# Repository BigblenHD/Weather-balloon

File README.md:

# Atmospheric Data Acquisition — Weather Balloon

Embedded firmware and custom PCB design for an atmospheric measurement payload, developed as a school project in Luxembourg.

**My contribution:** firmware development, PCB design and technical project delivery. The project brought together sensor integration, data logging, electronics assembly and launch preparation.

## Flight outcome

The original team log records a launch from Redange on **14 September 2024**, followed by recovery near Verdun, France, roughly two hours later. The payload, camera and SD card were recovered intact. The flight dataset is not included in this repository.

## Engineering work

- Integrated environmental and motion sensors using I²C and SPI.
- Developed Arduino sketches for individual sensor checks and combined acquisition.
- Implemented timestamped SD-card logging and LED status indications.
- Designed the data-logger schematic and board layout in EAGLE.

## Start here

| Area | Files | What to review |
| --- | --- | --- |
| Combined acquisition | [`all_in_one.ino`](Prep_launch/Module_software_tests/all_in_one/all_in_one.ino) | Environmental sensors, IMU, ozone, gamma sensor, PT100, RTC and SD integration |
| Smaller logger variant | [`Final_Code.ino`](Prep_launch/Final%20Code/Final_Code.ino) | BMP280 + MPU6050 acquisition and CSV-style logging |
| Hardware | [PCB files](Prep_launch/PCB) | EAGLE `.sch` schematic and `.brd` layout |
| Component experiments | [Module tests](Prep_launch/Module_software_tests) | Isolated checks and calibration sketches |

## Hardware and dependencies

The repository contains several hardware revisions. Select dependencies for the sketch you are examining; the sketches are not interchangeable.

| Sketch | Components / libraries |
| --- | --- |
| `all_in_one.ino` | Adafruit MS8607, Adafruit Unified Sensor, DFRobot OzoneSensor, Arduino LSM9DS1, Adafruit MAX31865, RTClib, SD, Wire and SPI; GDK101 access is implemented in the sketch |
| `Final_Code.ino` | MPU6050_light, Adafruit BMP280 and its dependencies, SD, Wire and SPI |

Use the Arduino IDE and a board core compatible with the selected hardware. Board selection, library versions, wiring and calibration must be matched to the original build; a reproducible build configuration is not yet recorded.

## Working with the code

1. Start with the individual [module tests](Prep_launch/Module_software_tests) to understand each peripheral.
2. Install the libraries used by your chosen sketch.
3. Match sensor addresses, chip-select pins and LED pins to the board schematic.
4. Open the sketch in the Arduino IDE, keeping any companion `.h` and `.cpp` files together.
5. Check serial output and SD logging on the bench before combining peripherals.

The folder name `Final Code` describes a historical revision. Its sketch uses BMP280 and MPU6050 sensors; the broader acquisition sketch lives under `Module_software_tests/all_in_one`.

## Project status

This repository preserves the project firmware and PCB sources. It includes experiments as well as integrated sketches, rather than a single packaged application. Measured sensor accuracy, exact dependency versions and flight-data analysis are not documented here.

## Team and acknowledgements

- **Ben Lies:** programming, PCB design and technical project delivery.
- **Ben Kasel:** mentoring, organisation, communication and troubleshooting.
- **Christophe Mayers:** soldering, project support and the original written project log.

The original log also mentions additional participants without naming them. This list reflects the credits currently documented in the repository.

[Original project log](https://github.com/BigblenHD/Weather-balloon/blob/688e36f4c935f01a88b4a0122774435af6ce9a63/README.md) · [Ben's portfolio](https://benlies.com)

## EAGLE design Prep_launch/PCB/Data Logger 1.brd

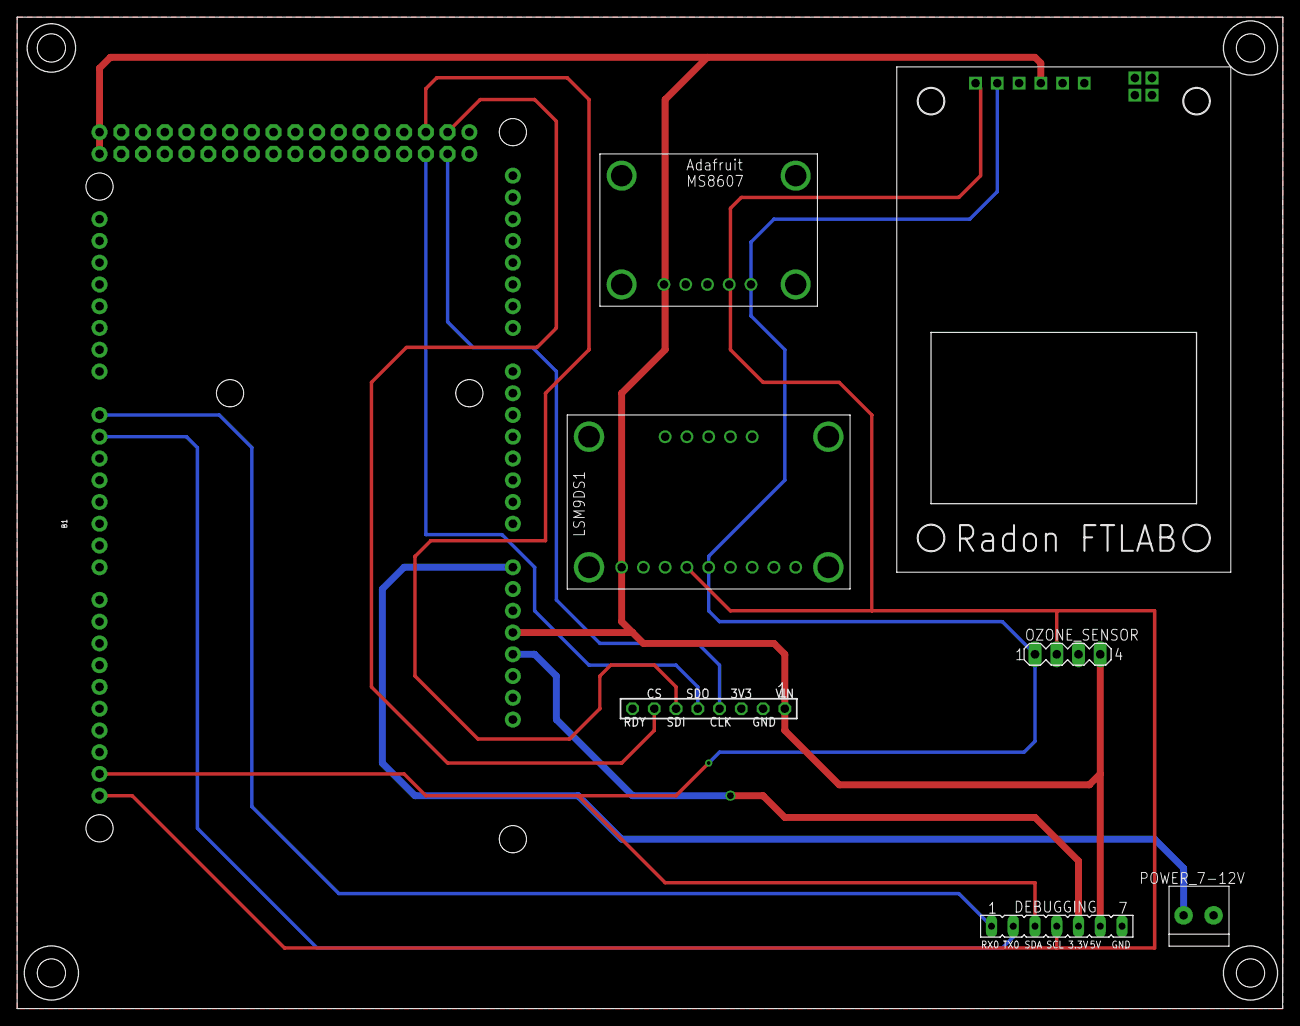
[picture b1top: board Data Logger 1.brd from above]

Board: 2 copper layers, 147.8 x 115.8 mm, 8 parts (0 on the bottom side), 12 nets.

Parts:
B1: ARDUINO_MEGA_R3FULL; ARDUINO_MEGA_NO_SILK
DEBUGGING: FE07
OZONE_SENSOR: OZONE_SENSOR; MA04-1
POWER_7-12V: 1X2-3.5MM
PRESSURE_SENSOR: ADAFRUIT_MS8607
U$1: FTLAB_GAMMA_SENSOR_MODULETHROUGH_HOLE; FTLAB_GAMMA_SENSOR_MODULE
U$2: ADAFRUIT_LSM9DS1
X3: Temperature Sensor Amplifier; SSW-108-02-G-S

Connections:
3.3V: B1.3.3V, DEBUGGING.5
5V: B1.5V, B1.5V@1, B1.5V@2, DEBUGGING.6, OZONE_SENSOR.4, PRESSURE_SENSOR.P$5, U$1.3, U$2.1, X3.1
CLK: B1.52, X3.4
CS: B1.53, X3.7
GND: B1.GND, B1.GND@1, B1.GND@2, B1.GND@3, B1.GND@4, DEBUGGING.7, OZONE_SENSOR.3, POWER_7-12V.1, PRESSURE_SENSOR.P$7, U$1.4, U$2.3, X3.2
RX0: B1.0, DEBUGGING.1
SCL1: B1.SCL, DEBUGGING.4, OZONE_SENSOR.2, PRESSURE_SENSOR.P$8, U$1.6, U$2.4
SDA1: B1.SDA, DEBUGGING.3, OZONE_SENSOR.1, PRESSURE_SENSOR.P$9, U$1.5, U$2.5
SDI: B1.51, X3.6
SDO: B1.50, X3.5
TX0: B1.1, DEBUGGING.2
VIN: B1.VIN, POWER_7-12V.2

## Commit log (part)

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2023-03-15 Create MPU6050_raw_data
2024-07-25 Create BRAND NEW CODE
2024-08-26 Final code
    Fixing that modules with SPI eat each other. Modules work together now. Fancy light to check initialisation. (Red is bad)
2024-08-26 Readme
    A short readme that may be changed in the future.
2024-09-15 Update README.md
    plan to clean u the project
2024-09-16 Begin_of_organisation
    Structured project. Next:
    ask ben for PCB file
    revise his code
    add readme file for hardware
2024-09-16 Test
2024-09-16 clean_up

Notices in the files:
parts and their libraries:
SparkFun-Boards: Licensing: Creative Commons ShareAlike 4.0 International - https://creativecommons.org/licenses/by-sa/4.0
